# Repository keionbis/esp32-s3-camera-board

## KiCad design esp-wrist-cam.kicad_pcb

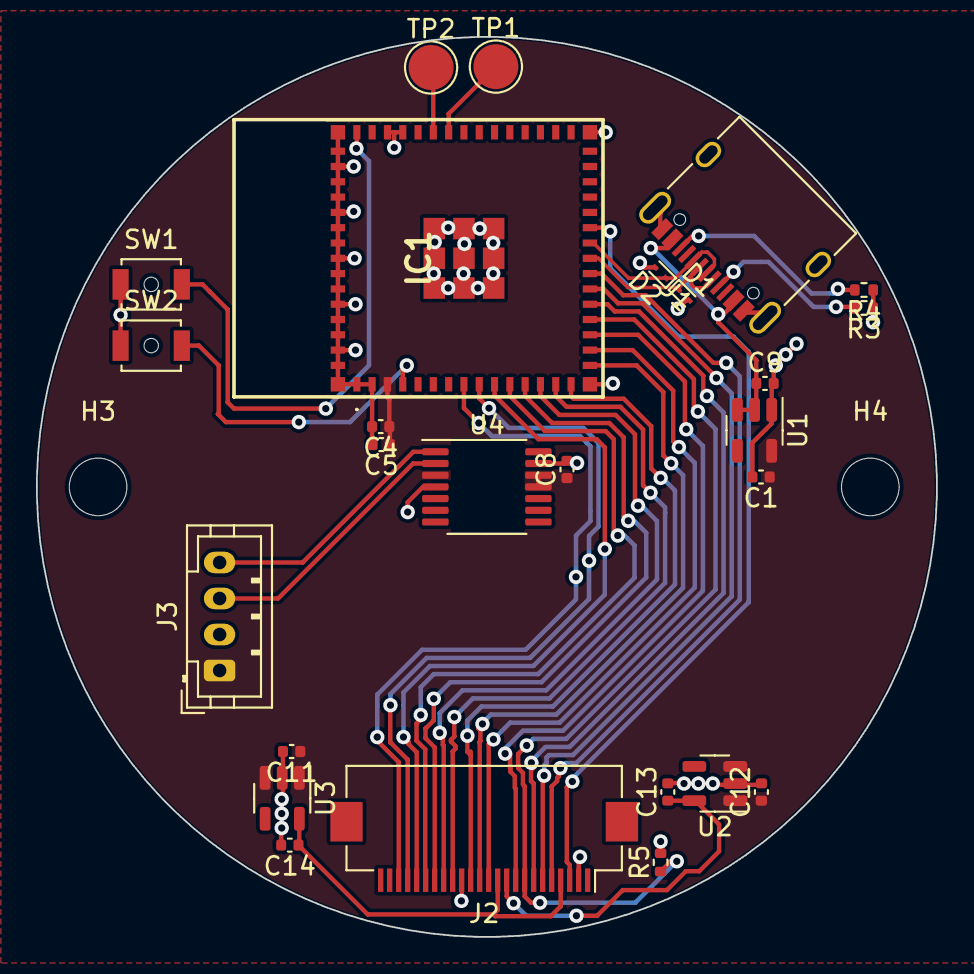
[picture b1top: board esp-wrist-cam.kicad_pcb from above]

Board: 2 copper layers, 50.0 x 50.0 mm, 30 parts (0 on the bottom side), 31 nets.

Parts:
C1, C5, C8, C9, C11, C12, C13, C14: 1uF; C_0402_1005Metric
C4: 0.1uF; C_0402_1005Metric
D1, D2: SZESD9B5.0ST5G; D_SOD-923
H1, H2, H3, H4: MountingHole; MountingHole_3.2mm_M3
IC1: ESP32-S3-MINI-1-N8; ESP32S3MINI1N8
J1: USB_C_Receptacle_USB2.0; USB_C_Receptacle_XKB_U262-16XN-4BVC11
J2: Conn_01x24_Female; Hirose_FH12-24S-0.5SH_1x24-1MP_P0.50mm_Horizontal
J3: I2C ENCODER; JST_PH_B4B-PH-K_1x04_P2.00mm_Vertical
R3, R4: 5.1K; R_0402_1005Metric
R5: 10K; R_0402_1005Metric
SW1, SW2: SW_SPST; SW_SPST_B3U-1000P-B
TP1, TP2: TestPoint; TestPoint_Pad_D2.5mm
U1: ADP7182AUJZ-3.3; TSOT-23-5
U2: TLV713185PDBV; SOT-23-5
U3: MIC5504-2.8YM5; SOT-23-5
U4: AS5048B; TSSOP-14_4.4x5mm_P0.65mm

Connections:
+1V5: C13.1, J2.10, U2.5 (OUT)
+2V8: C14.1, J2.4, J2.11, U3.5 (VOUT)
+3.3V: C1.1, C4.1, C5.1, C8.1, C11.1, C12.1, IC1.3 (3V3), J3.1, U1.5 (VOUT), U2.1 (IN), U2.3 (EN), U3.1 (VIN), U3.3 (EN), U4.3 (A2), U4.11 (VDD5V), U4.12 (VDD3V)
+5V: C9.1, J1.A4 (VBUS), J1.A9 (VBUS), J1.B4 (VBUS), J1.B9 (VBUS), U1.2 (VIN), U1.3 (EN)
/Camera/HREF: IC1.18 (IO14), J2.9
/Camera/PCLK: IC1.13 (IO9), J2.17
/Camera/PWDN: IC1.19 (IO15), J2.8, R5.1
/Camera/RESET: IC1.21 (IO17), J2.6
/Camera/SCL: IC1.22 (IO18), J2.5
/Camera/SDA: IC1.25 (IO21), J2.3
/Camera/VSYNC: IC1.20 (IO16), J2.7
/Camera/XCLK: IC1.16 (IO12), J2.13
/Camera/Y2: IC1.11 (IO7), J2.19
/Camera/Y3: IC1.9 (IO5), J2.21
/Camera/Y4: IC1.8 (IO4), J2.22
/Camera/Y5: IC1.10 (IO6), J2.20
/Camera/Y6: IC1.12 (IO8), J2.18
/Camera/Y7: IC1.14 (IO10), J2.16
/Camera/Y8: IC1.15 (IO11), J2.14
/Camera/Y9: IC1.17 (IO13), J2.12
/I2C_SCL: J3.3, U4.2 (SCL)
/I2C_SDA: J3.4, U4.1 (SDA)
/MCU/CC1: J1.A5 (CC1), R3.2
/MCU/CC2: J1.B5 (CC2), R4.2
/MCU/D_N: D1.1 (A1), IC1.23 (IO19), J1.A7 (D-), J1.B7 (D-)
/MCU/D_P: D2.1 (A1), IC1.24 (IO20), J1.A6 (D+), J1.B6 (D+)
/MCU/IO0: IC1.4 (IO0), SW2.2 (B)
/MCU/RESET: IC1.45 (EN), SW1.2 (B)
/MCU/RX0: IC1.40 (RXD0), TP2.1
/MCU/TX0: IC1.39 (TXD0), TP1.1
GND: C1.2, C4.2, C5.2, C8.2, C9.2, C11.2, C12.2, C13.2, C14.2, D1.2 (A2), D2.2 (A2), IC1.1 (GND_1), IC1.2 (GND_2), IC1.42 (GND_3), IC1.43 (GND_4), IC1.46 (GND_5), IC1.47 (GND_6), IC1.48 (GND_7), IC1.49 (GND_8), IC1.50 (GND_9), IC1.51 (GND_10), IC1.52 (GND_11), IC1.53 (GND_12), IC1.54 (GND_13), IC1.55 (GND_14), IC1.56 (GND_15), IC1.57 (GND_16), IC1.58 (GND_17), IC1.59 (GND_18), IC1.60 (GND_19), IC1.61 (GND_20), IC1.62 (GND_21), IC1.63 (GND_22), IC1.64 (GND_23), IC1.65 (GND_24), IC1.66 (GND_25), IC1.67 (GND_26), IC1.68 (GND_27), IC1.69 (GND_28), IC1.70 (GND_29), IC1.71 (GND_30), IC1.72 (GND_31), IC1.73 (GND_32), J1.A1 (GND), J1.A12 (GND), J1.B1 (GND), J1.B12 (GND), J1.S1 (SHIELD), J2.2, J2.15, J3.2, R3.1, R4.1, R5.2, SW1.1 (A), SW2.1 (A), U1.1 (GND), U2.2 (GND), U3.2 (GND), U4.4 (A1), U4.13 (GND)

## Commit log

2022-08-31 finished routing
